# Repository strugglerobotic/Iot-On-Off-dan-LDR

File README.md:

# Iot-On-Off-dan-LDR
Project Yang Bertujuan Untuk Mematikan Dan Menyalakan Lampu Melalui Wifi Baik Koeksi Lokal Maupun Internet Dengan Fitur Tambahan LDR

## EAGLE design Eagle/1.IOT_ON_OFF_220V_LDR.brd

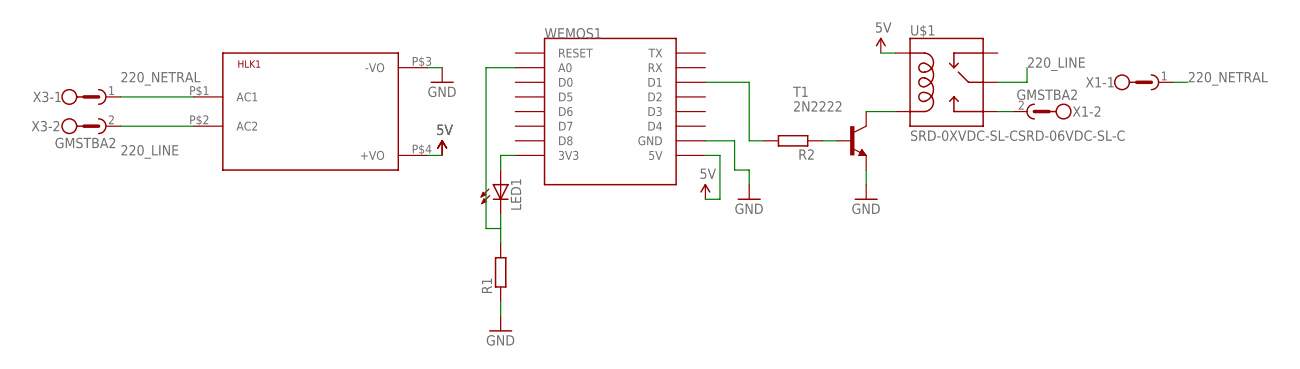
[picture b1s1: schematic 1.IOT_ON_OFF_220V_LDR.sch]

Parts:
HLK1: HLK-PM013W; HLK-PM01
LED1: LED5MM
R1, R2: R-EU_0207_10; 0207/10
T1: 2N2222; TO18
U$1: SRD-0XVDC-SL-CSRD-06VDC-SL-C; SRD-0XVDC-SL-C
WEMOS1: WEMOS-D1-MINI
X1, X3: GMSTBA2

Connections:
5V: HLK1.P$4 (+VO), U$1.COIL1, WEMOS1.5V
220_LINE: HLK1.P$2 (AC2), U$1.SWCOMMON, X3.2
220_NETRAL: HLK1.P$1 (AC1), X1.1, X3.1
GND: HLK1.P$3 (-VO), R1.1, T1.1 (E), WEMOS1.GND
unnamed: U$1.SWOPEN, X1.2
unnamed: R2.2, WEMOS1.D1
unnamed: T1.3 (C), U$1.COIL0
unnamed: LED1.A, WEMOS1.3V3
unnamed: LED1.K (C), R1.2, WEMOS1.A0
unnamed: R2.1, T1.2 (B)

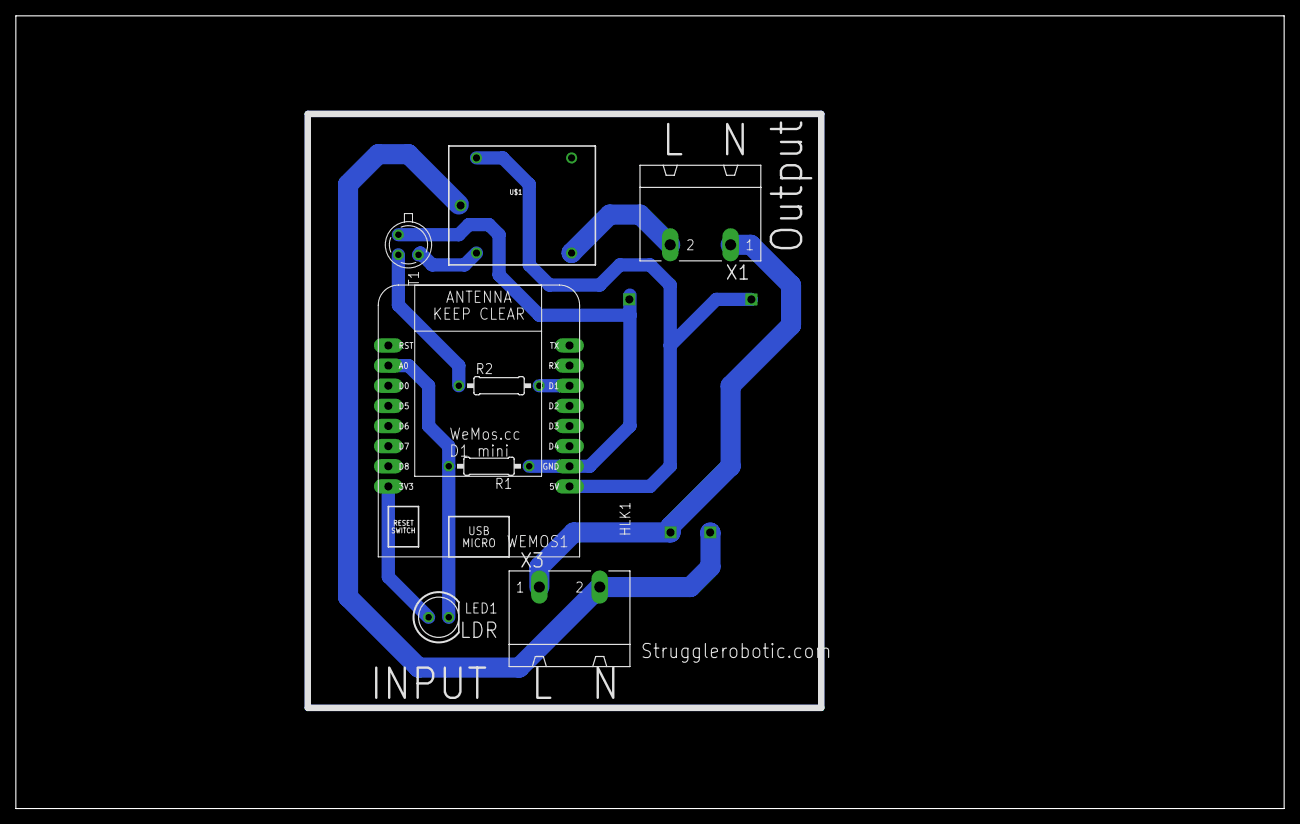
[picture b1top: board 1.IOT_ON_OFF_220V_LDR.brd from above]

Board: 2 copper layers, 160.0 x 100.0 mm, 9 parts (0 on the bottom side), 10 nets.

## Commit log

2020-05-09 Folder Eagle , Isi Rangkaian Schematic
2020-05-09 Schematic Dan Board

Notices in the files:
parts and their libraries:
SparkFun-Aesthetics: Licensing: Creative Commons ShareAlike 4.0 International - https://creativecommons.org/licenses/by-sa/4.0
